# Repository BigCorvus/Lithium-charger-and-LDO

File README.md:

# Lithium-charger-and-LDO
This is a circuit that is used very often. It features a MCP73831 lithium charging IC capable of charging currents up to 500mA and a generic SOT23-5 LDO. I chose ultra low quiescent current mudels such as XC6215 in the 3.3V variant so the circuit can provide 3.3V all the time and last for ages

Update: version v1.1 is even smaller and contains some substantial improvements: you can switch off the LDO and the voltage divider (which will otherwise consuming power) via an external switch while still maintaining charging capability of the battery. All USB data lines are broken out to test pads.

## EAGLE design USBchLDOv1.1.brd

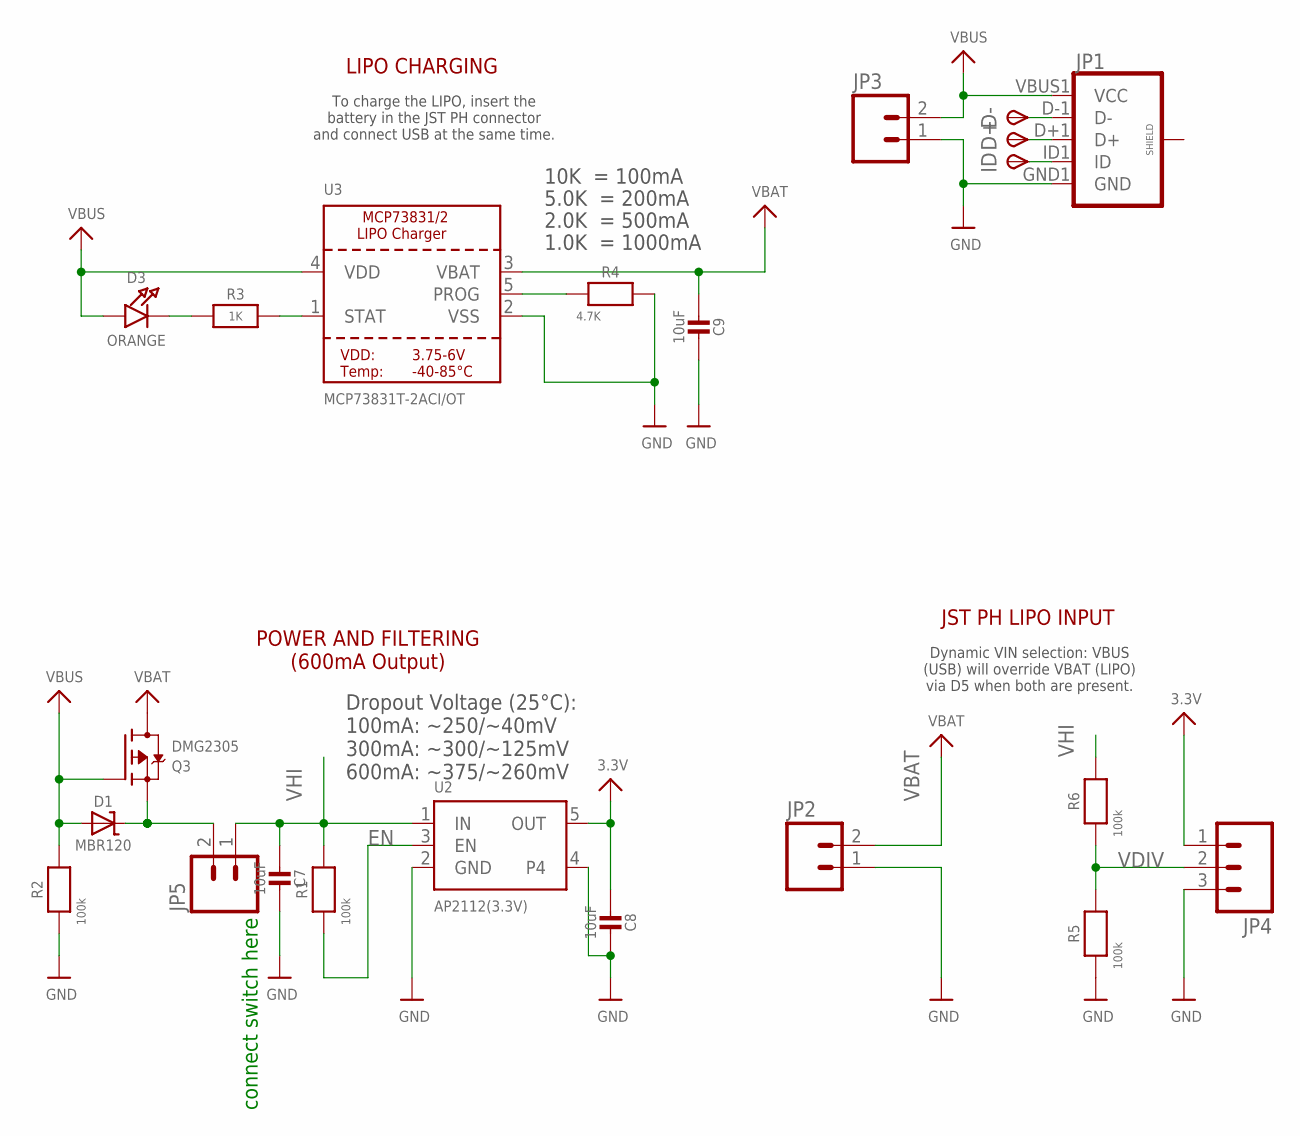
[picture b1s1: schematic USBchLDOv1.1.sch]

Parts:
C7, C8, C9: 10uF; 0805-NO
D1: MBR120; SOD-123
D3: ORANGE; CHIPLED_0805_NOOUTLINE
D+: TPSTP09R; TP09R
D-: TPSTP09R; TP09R
ID: TPSTP09R; TP09R
JP1: USB_MICROB_PLUGCONN-11752; USB-B-MICRO-SMD_V03
JP2, JP3, JP5: M02PTH; 1X02
JP4: M03PTH; 1X03
Q3: DMG2305; SOT23-R
R1, R2, R5, R6: 100k; 0603-NO
R3: 1K; 0603-NO
R4: 4.7K; 0603-NO
U2: AP2112(3.3V); SOT23-5
U3: MCP73831T-2ACI/OT; SOT23-5

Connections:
3.3V: C8.2, JP4.1, U2.5 (OUT)
EN: R1.1, U2.3 (EN)
GND: C7.1, C8.1, C9.1, JP1.GND1 (GND), JP2.1, JP3.1, JP4.3, R2.1, R4.2, R5.1, U2.2 (GND), U2.4, U3.2 (VSS)
unnamed: D3.C, R3.1
unnamed: ID.TP, JP1.ID1 (ID)
unnamed: D+.TP, JP1.D+1 (D+)
unnamed: D-.TP, JP1.D-1 (D-)
unnamed: D1.C, JP5.2, Q3.2 (S)
unnamed: R3.2, U3.1 (STAT)
unnamed: R4.1, U3.5 (PROG)
VBAT: C9.2, JP2.2, Q3.3 (D), U3.3 (VBAT)
VBUS: D1.A, D3.A, JP1.VBUS1 (VCC), JP3.2, Q3.1 (G), R2.2, U3.4 (VDD)
VDIV: JP4.2, R5.2, R6.1
VHI: C7.2, JP5.1, R1.2, R6.2, U2.1 (IN)

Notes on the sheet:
POWER AND FILTERING (600mA Output)
Dropout Voltage (25°C): 100mA: ~250/~40mV 300mA: ~300/~125mV 600mA: ~375/~260mV
10K = 100mA
5.0K = 200mA
2.0K = 500mA
1.0K = 1000mA
LIPO CHARGING
To charge the LIPO, insert the battery in the JST PH connector and connect USB at the same time.
JST PH LIPO INPUT
Dynamic VIN selection: VBUS (USB) will override VBAT (LIPO) via D5 when both are present.
connect switch here

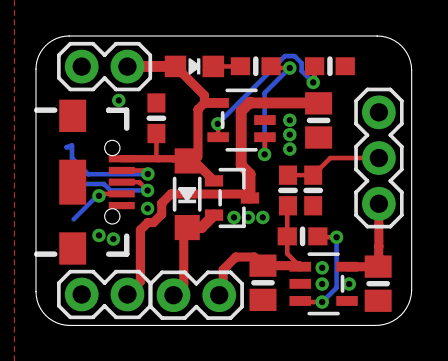
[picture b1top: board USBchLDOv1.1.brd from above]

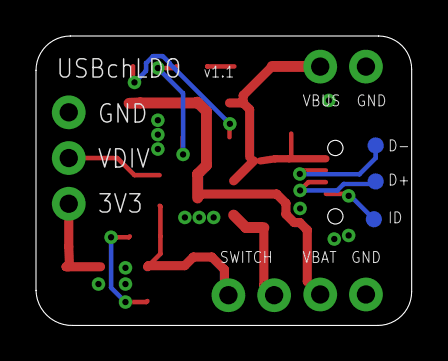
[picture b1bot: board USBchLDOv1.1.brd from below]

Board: 2 copper layers, 20.9 x 16.1 mm, 22 parts (3 on the bottom side), 14 nets.

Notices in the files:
parts and their libraries:
microbuilder: This work is placed in the public domain, and may be freely used for commercial and non-commercial work with the following conditions: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
SparkFun-Connectors: Licensing: Creative Commons ShareAlike 4.0 International - https://creativecommons.org/licenses/by-sa/4.0
